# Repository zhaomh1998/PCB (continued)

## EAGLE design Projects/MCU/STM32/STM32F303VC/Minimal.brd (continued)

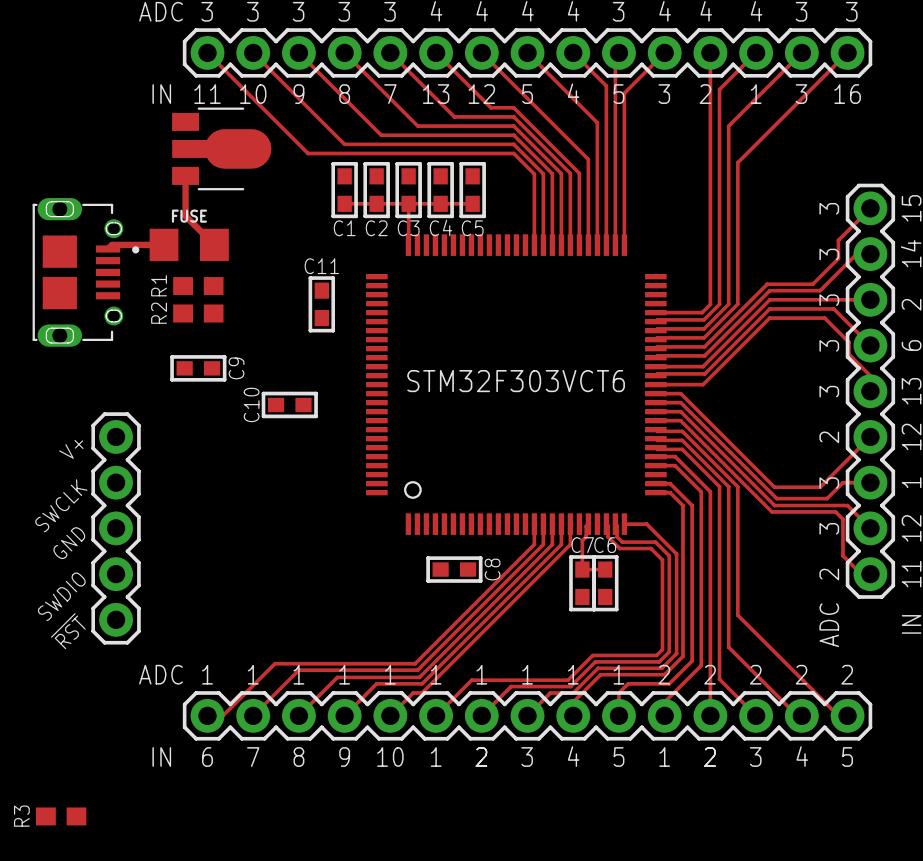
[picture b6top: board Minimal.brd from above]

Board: 2 copper layers, 22 parts (0 on the bottom side), 51 nets.

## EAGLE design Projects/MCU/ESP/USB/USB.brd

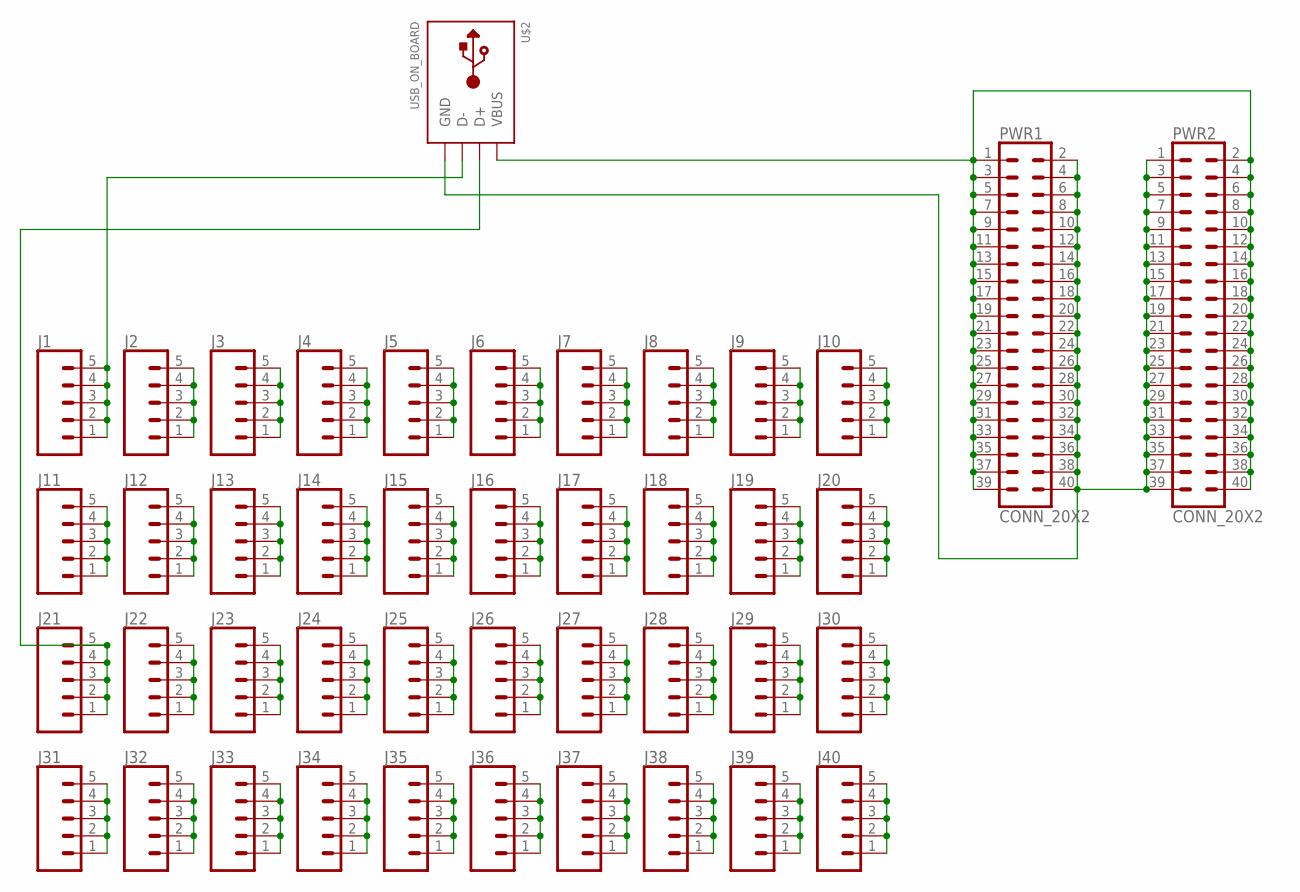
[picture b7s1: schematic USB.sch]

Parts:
J1, J2, J3, J4, J5, J6, J7, J8, J9, J10, J11, J12, J13, J14, J15, J16, J17, J18, J19, J20, J21, J22, J23, J24, J25, J26, J27, J28, J29, J30, J31, J32, J33, J34, J35, J36, J37, J38, J39, J40: CONN_05; 1X05
PWR1, PWR2: CONN_20X2; 2X20
U$2: USB_ON_BOARD

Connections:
unnamed: J1.1, J1.2, J1.3, J1.4, J1.5, U$2.D-
unnamed: J2.1, J2.2, J2.3, J2.4, J2.5
unnamed: J3.1, J3.2, J3.3, J3.4, J3.5
unnamed: J4.1, J4.2, J4.3, J4.4, J4.5
unnamed: J5.1, J5.2, J5.3, J5.4, J5.5
unnamed: J6.1, J6.2, J6.3, J6.4, J6.5
unnamed: J7.1, J7.2, J7.3, J7.4, J7.5
unnamed: J8.1, J8.2, J8.3, J8.4, J8.5
unnamed: J9.1, J9.2, J9.3, J9.4, J9.5
unnamed: J10.1, J10.2, J10.3, J10.4, J10.5
unnamed: J11.1, J11.2, J11.3, J11.4, J11.5
unnamed: J12.1, J12.2, J12.3, J12.4, J12.5
unnamed: J13.1, J13.2, J13.3, J13.4, J13.5
unnamed: J14.1, J14.2, J14.3, J14.4, J14.5
unnamed: J15.1, J15.2, J15.3, J15.4, J15.5
unnamed: J16.1, J16.2, J16.3, J16.4, J16.5
unnamed: J17.1, J17.2, J17.3, J17.4, J17.5
unnamed: J18.1, J18.2, J18.3, J18.4, J18.5
unnamed: J19.1, J19.2, J19.3, J19.4, J19.5
unnamed: J20.1, J20.2, J20.3, J20.4, J20.5
unnamed: J21.1, J21.2, J21.3, J21.4, J21.5, U$2.D+
unnamed: J22.1, J22.2, J22.3, J22.4, J22.5
unnamed: J23.1, J23.2, J23.3, J23.4, J23.5
unnamed: J24.1, J24.2, J24.3, J24.4, J24.5
unnamed: J25.1, J25.2, J25.3, J25.4, J25.5
unnamed: J26.1, J26.2, J26.3, J26.4, J26.5
unnamed: J27.1, J27.2, J27.3, J27.4, J27.5
unnamed: J28.1, J28.2, J28.3, J28.4, J28.5
unnamed: J29.1, J29.2, J29.3, J29.4, J29.5
unnamed: J30.1, J30.2, J30.3, J30.4, J30.5
unnamed: J31.1, J31.2, J31.3, J31.4, J31.5
unnamed: J32.1, J32.2, J32.3, J32.4, J32.5
unnamed: J33.1, J33.2, J33.3, J33.4, J33.5
unnamed: J34.1, J34.2, J34.3, J34.4, J34.5
unnamed: J35.1, J35.2, J35.3, J35.4, J35.5
unnamed: J36.1, J36.2, J36.3, J36.4, J36.5
unnamed: J37.1, J37.2, J37.3, J37.4, J37.5
unnamed: J38.1, J38.2, J38.3, J38.4, J38.5
unnamed: J39.1, J39.2, J39.3, J39.4, J39.5
unnamed: J40.1, J40.2, J40.3, J40.4, J40.5
unnamed: PWR1.1, PWR1.3, PWR1.5, PWR1.7, PWR1.9, PWR1.11, PWR1.13, PWR1.15, PWR1.17, PWR1.19, PWR1.21, PWR1.23, PWR1.25, PWR1.27, PWR1.29, PWR1.31, PWR1.33, PWR1.35, PWR1.37, PWR1.39, PWR2.2, PWR2.4, PWR2.6, PWR2.8, PWR2.10, PWR2.12, PWR2.14, PWR2.16, PWR2.18, PWR2.20, PWR2.22, PWR2.24, PWR2.26, PWR2.28, PWR2.30, PWR2.32, PWR2.34, PWR2.36, PWR2.38, PWR2.40, U$2.VCC (VBUS)
unnamed: PWR1.2, PWR1.4, PWR1.6, PWR1.8, PWR1.10, PWR1.12, PWR1.14, PWR1.16, PWR1.18, PWR1.20, PWR1.22, PWR1.24, PWR1.26, PWR1.28, PWR1.30, PWR1.32, PWR1.34, PWR1.36, PWR1.38, PWR1.40, PWR2.1, PWR2.3, PWR2.5, PWR2.7, PWR2.9, PWR2.11, PWR2.13, PWR2.15, PWR2.17, PWR2.19, PWR2.21, PWR2.23, PWR2.25, PWR2.27, PWR2.29, PWR2.31, PWR2.33, PWR2.35, PWR2.37, PWR2.39, U$2.GND

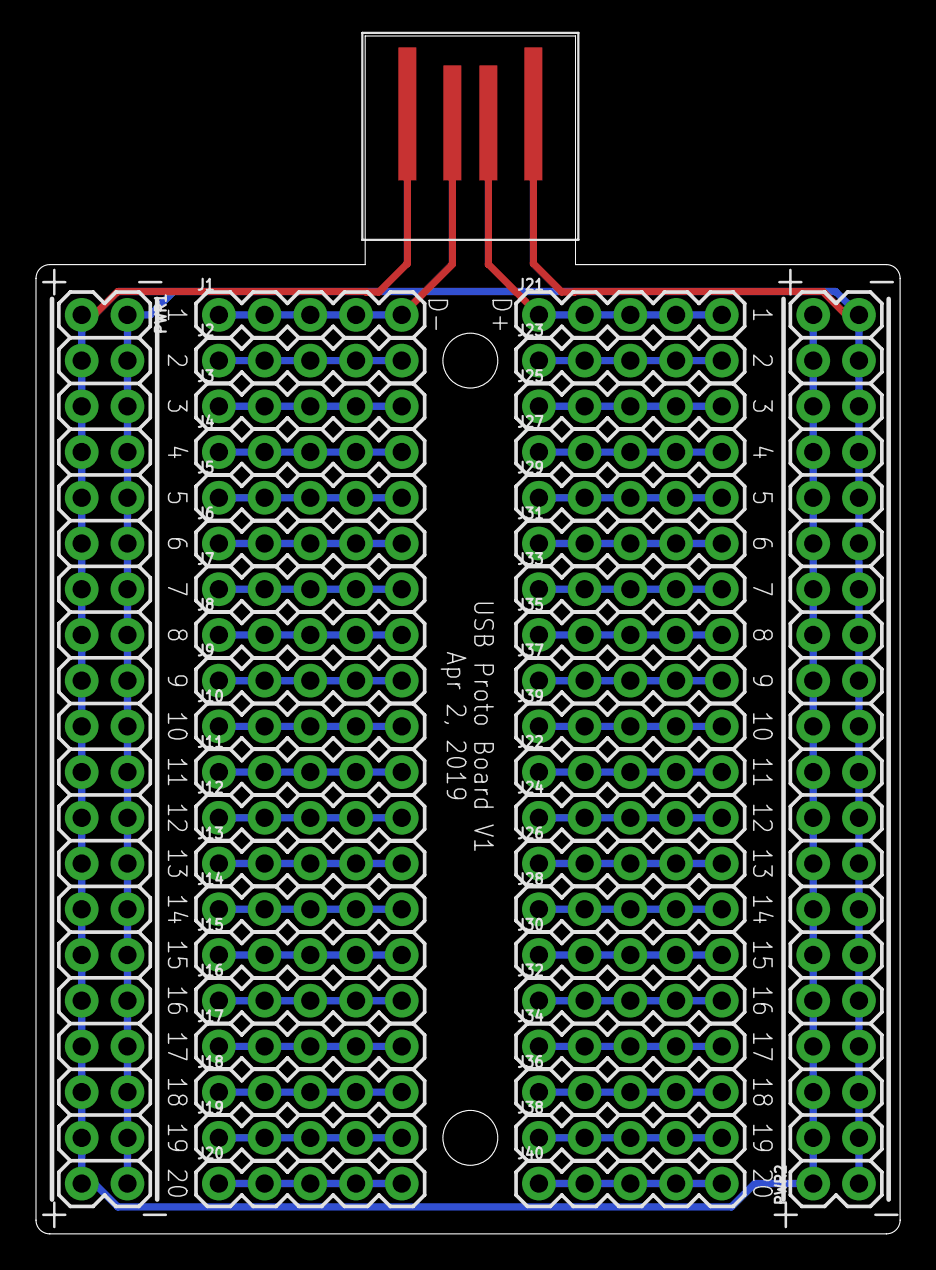
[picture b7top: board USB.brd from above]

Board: 2 copper layers, 48.0 x 66.5 mm, 43 parts (0 on the bottom side), 42 nets.

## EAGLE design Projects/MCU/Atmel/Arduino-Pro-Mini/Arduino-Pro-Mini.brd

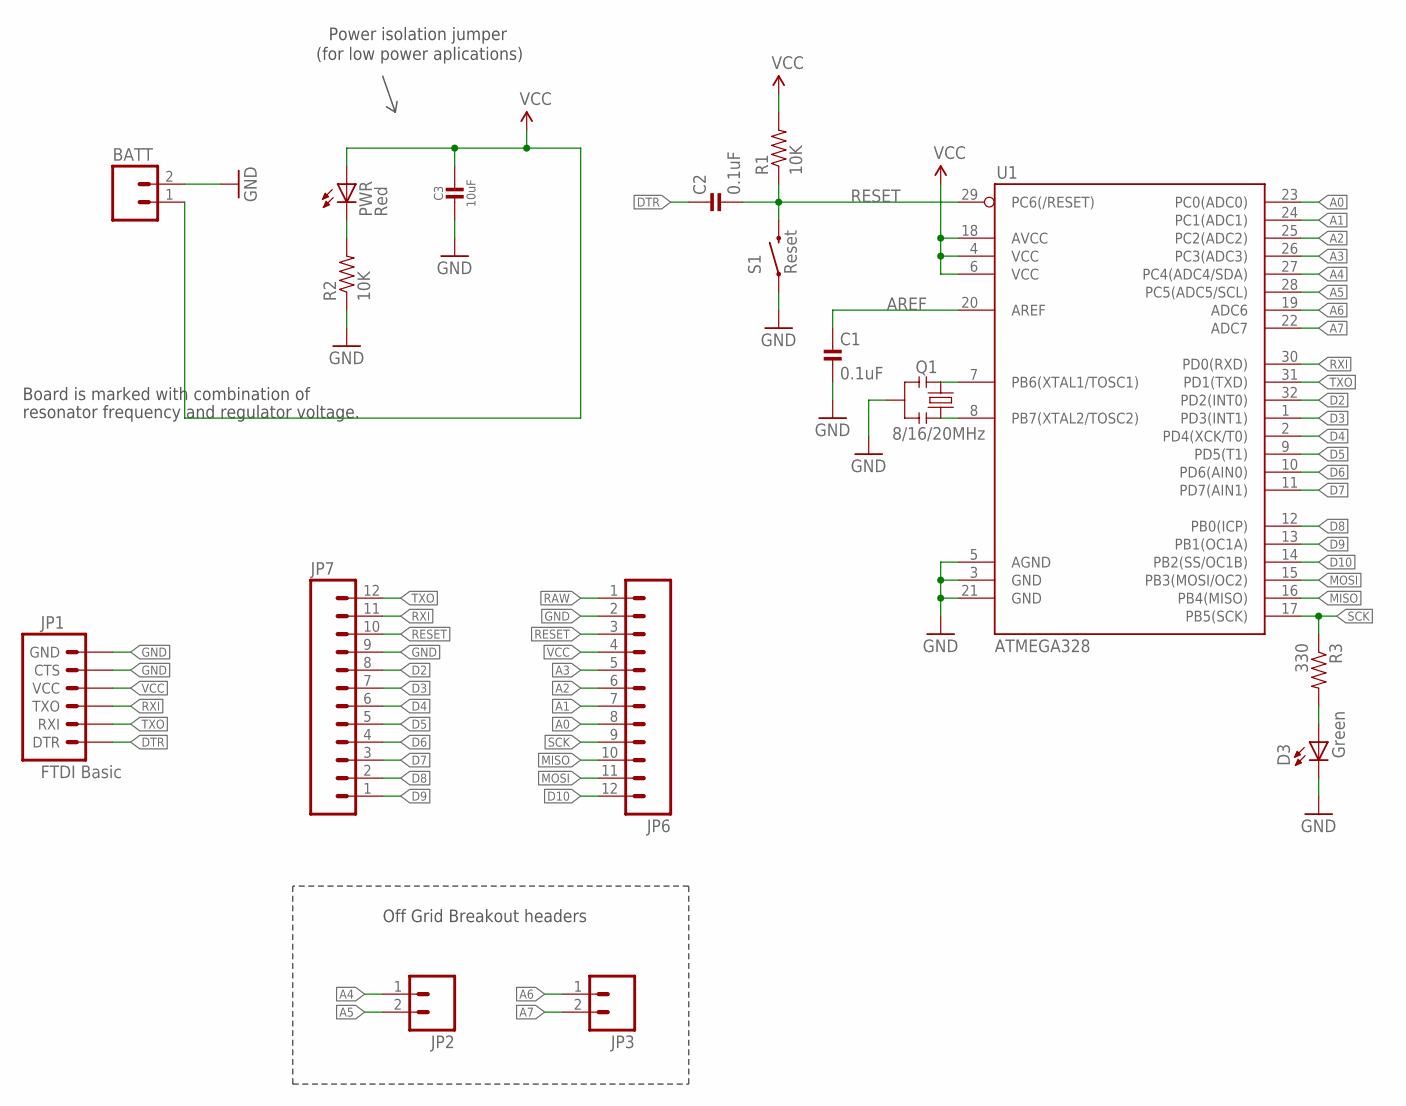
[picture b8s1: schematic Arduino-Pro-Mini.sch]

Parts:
BATT: M02PTH; 1X02
C1, C2: 0.1uF; CAP_0603
C3: 10uF; CAP_0805
D3: Green; 0603-LED-ALT1
JP1: FTDI Basic; 1X06
JP2, JP3: M02PTH; 1X02
JP6, JP7: M12PTH; 1X12
PWR: Red; 0603-LED-ALT1
Q1: 8/16/20MHz; RESONATOR-SMD-1:1
R1, R2: 10K; 0603
R3: 330; 0603
S1: Reset; TACTILE_SWITCH_SMD_6.0X3.5MM
U1: ATMEGA328; TQFP32-08

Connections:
A0: JP6.8, U1.23 (PC0(ADC0))
A1: JP6.7, U1.24 (PC1(ADC1))
A2: JP6.6, U1.25 (PC2(ADC2))
A3: JP6.5, U1.26 (PC3(ADC3))
A4: JP2.1, U1.27 (PC4(ADC4/SDA))
A5: JP2.2, U1.28 (PC5(ADC5/SCL))
A6: JP3.1, U1.19 (ADC6)
A7: JP3.2, U1.22 (ADC7)
AREF: C1.2, U1.20 (AREF)
D2: JP7.8, U1.32 (PD2(INT0))
D3: JP7.7, U1.1 (PD3(INT1))
D4: JP7.6, U1.2 (PD4(XCK/T0))
D5: JP7.5, U1.9 (PD5(T1))
D6: JP7.4, U1.10 (PD6(AIN0))
D7: JP7.3, U1.11 (PD7(AIN1))
D8: JP7.2, U1.12 (PB0(ICP))
D9: JP7.1, U1.13 (PB1(OC1A))
D10: JP6.12, U1.14 (PB2(SS/OC1B))
DTR: C2.2, JP1.1 (DTR)
GND: BATT.2, C1.1, C3.2, D3.C, JP1.5 (CTS), JP1.6 (GND), JP6.2, JP7.9, Q1.2, R2.1, S1.1, U1.3 (GND), U1.5 (AGND), U1.21 (GND)
MISO: JP6.10, U1.16 (PB4(MISO))
MOSI: JP6.11, U1.15 (PB3(MOSI/OC2))
unnamed: Q1.3, U1.8 (PB7(XTAL2/TOSC2))
unnamed: Q1.1, U1.7 (PB6(XTAL1/TOSC1))
unnamed: PWR.C, R2.2
unnamed: D3.A, R3.2
RAW: JP6.1
RESET: C2.1, JP6.3, JP7.10, R1.1, S1.2, U1.29 (PC6(/RESET))
RXI: JP1.3 (TXO), JP7.11, U1.30 (PD0(RXD))
SCK: JP6.9, R3.1, U1.17 (PB5(SCK))
TXO: JP1.2 (RXI), JP7.12, U1.31 (PD1(TXD))
VCC: BATT.1, C3.1, JP1.4 (VCC), JP6.4, PWR.A, R1.2, U1.4 (VCC), U1.6 (VCC), U1.18 (AVCC)

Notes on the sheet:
Board is marked with combination of
resonator frequency and regulator voltage.
Off Grid Breakout headers
Power isolation jumper
(for low power aplications)

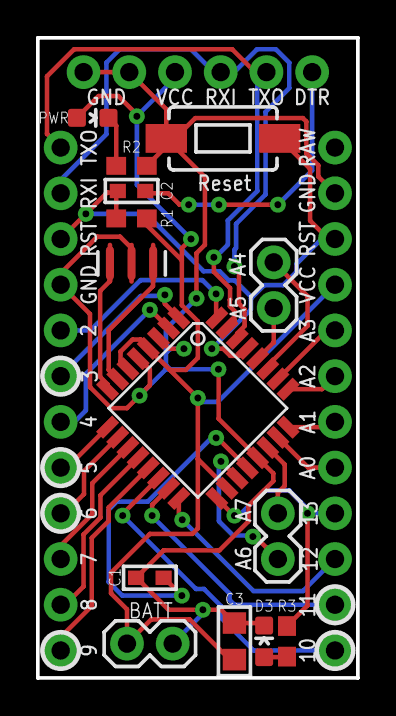
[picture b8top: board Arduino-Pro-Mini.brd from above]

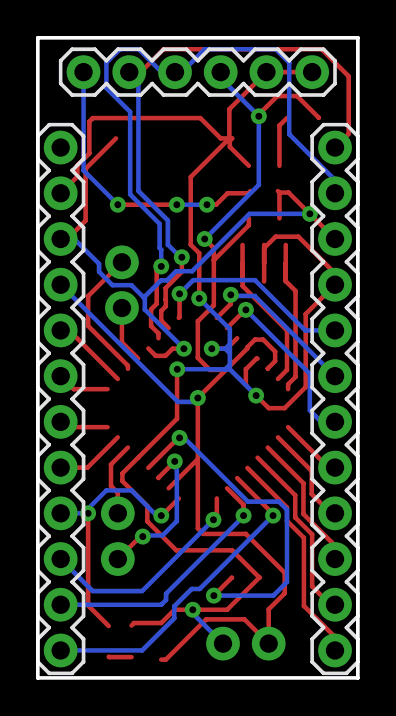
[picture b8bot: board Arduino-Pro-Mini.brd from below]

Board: 2 copper layers, 17.8 x 35.6 mm, 17 parts (3 on the bottom side), 31 nets.

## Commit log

2019-03-25 init
2019-03-25 add JST-1.25-6P
2019-03-25 cam, ESPFTDI V1, ESP Breakout V2
2019-04-09 update usb & Arduino pro mini
2019-04-13 pro mini board route
2019-04-24 update lib: microusb, PH 2P, typo fix
2019-05-03 update 7 pin JST and resistor array
2019-05-03 added SIM7000
2019-05-03 ESP32 LiPo USB board
2019-05-12 take out autoprgm
2019-06-09 add jlc dru, fix tiny font size, change QFN footprint to longer pad to prevent short
2019-07-05 clean up repo
2019-07-05 add flex sensor, stm32f302, svg and brd conversion ulp
2019-07-07 library: add stm32f3, ams small package, slight improvements
2019-07-07 line following robot proj init
2019-08-23 lots of lib components updates
2020-01-15 minor fixes, more parts
2020-02-23 eagle lib bump 2/22
2020-02-23 bump 2/22
2020-02-23 first assembly attempt!
2020-02-24 esp32 dbl
2020-02-24 bump eagle library 2/23
2020-07-22 bump library 7/22
2020-07-22 bump ESP32Tiny project
2020-07-28 add JLCPCB BOM and CPL file generation scripts
2020-07-28 revise JLCPCB 2 layer design rules
2020-07-28 add JLCPCB 4 layer DRU and CAM
2020-07-28 massive library updates to include JLCPCB Assembly parts with its LCSC ids
